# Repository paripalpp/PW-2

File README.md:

# PW-2
## parts
|     |     |
| --- | --- |
C7								|10n
C9, C10							|100u
C6, C8, C11						|1n
C1, C12                      	|10u
C2, C3, C5, C13, C16, C19-C25	|100n
C14, C15						|22p
C4, C17, C18					|1u
D1								|D
D2								|D_TVS
D3								|LED
D4-D7							|WS2812C
F1-F4							|Fuse
FL1								|BNX022
J1								|T_conn_male
J3								|USB_A_Stacked
J5								|2x07_P1.27mm_SMD
J6, J7							|S04B-XASK-1
J2, J8							|T_conn_female
J9-J13							|PinHeader_1x02_P2.54mm
J14-J20							|S02B-XASK-1
JP1								|SolderJumper_3_Bridged12
JP2-JP6							|SolderJumper_2_Open
L1								|8.2uH
Q1								|IPT007N06N
Q2, Q3							|TPH11006NL
R1								|100k
R4, R7, R8, R11, R12			|5k
R13								|100
R2, R3, R5, R6, R9, R10, R14-R16	|10k
R17								|120
R18								|10
R19								|330
RV1								|2.2k_Potentiometer
SW1								|SW_Push
SW2, SW3						|SW_SPDT
U1								|L7812
U2								|NCP1034
U3								|L78L12_SOT89
U4								|MCP1700-3302E_SOT23
U5								|STM32F303K8Tx
U6								|IM920s
U7								|MCP2551-I-SN
U8								|TLP152
Y1								|16MHz

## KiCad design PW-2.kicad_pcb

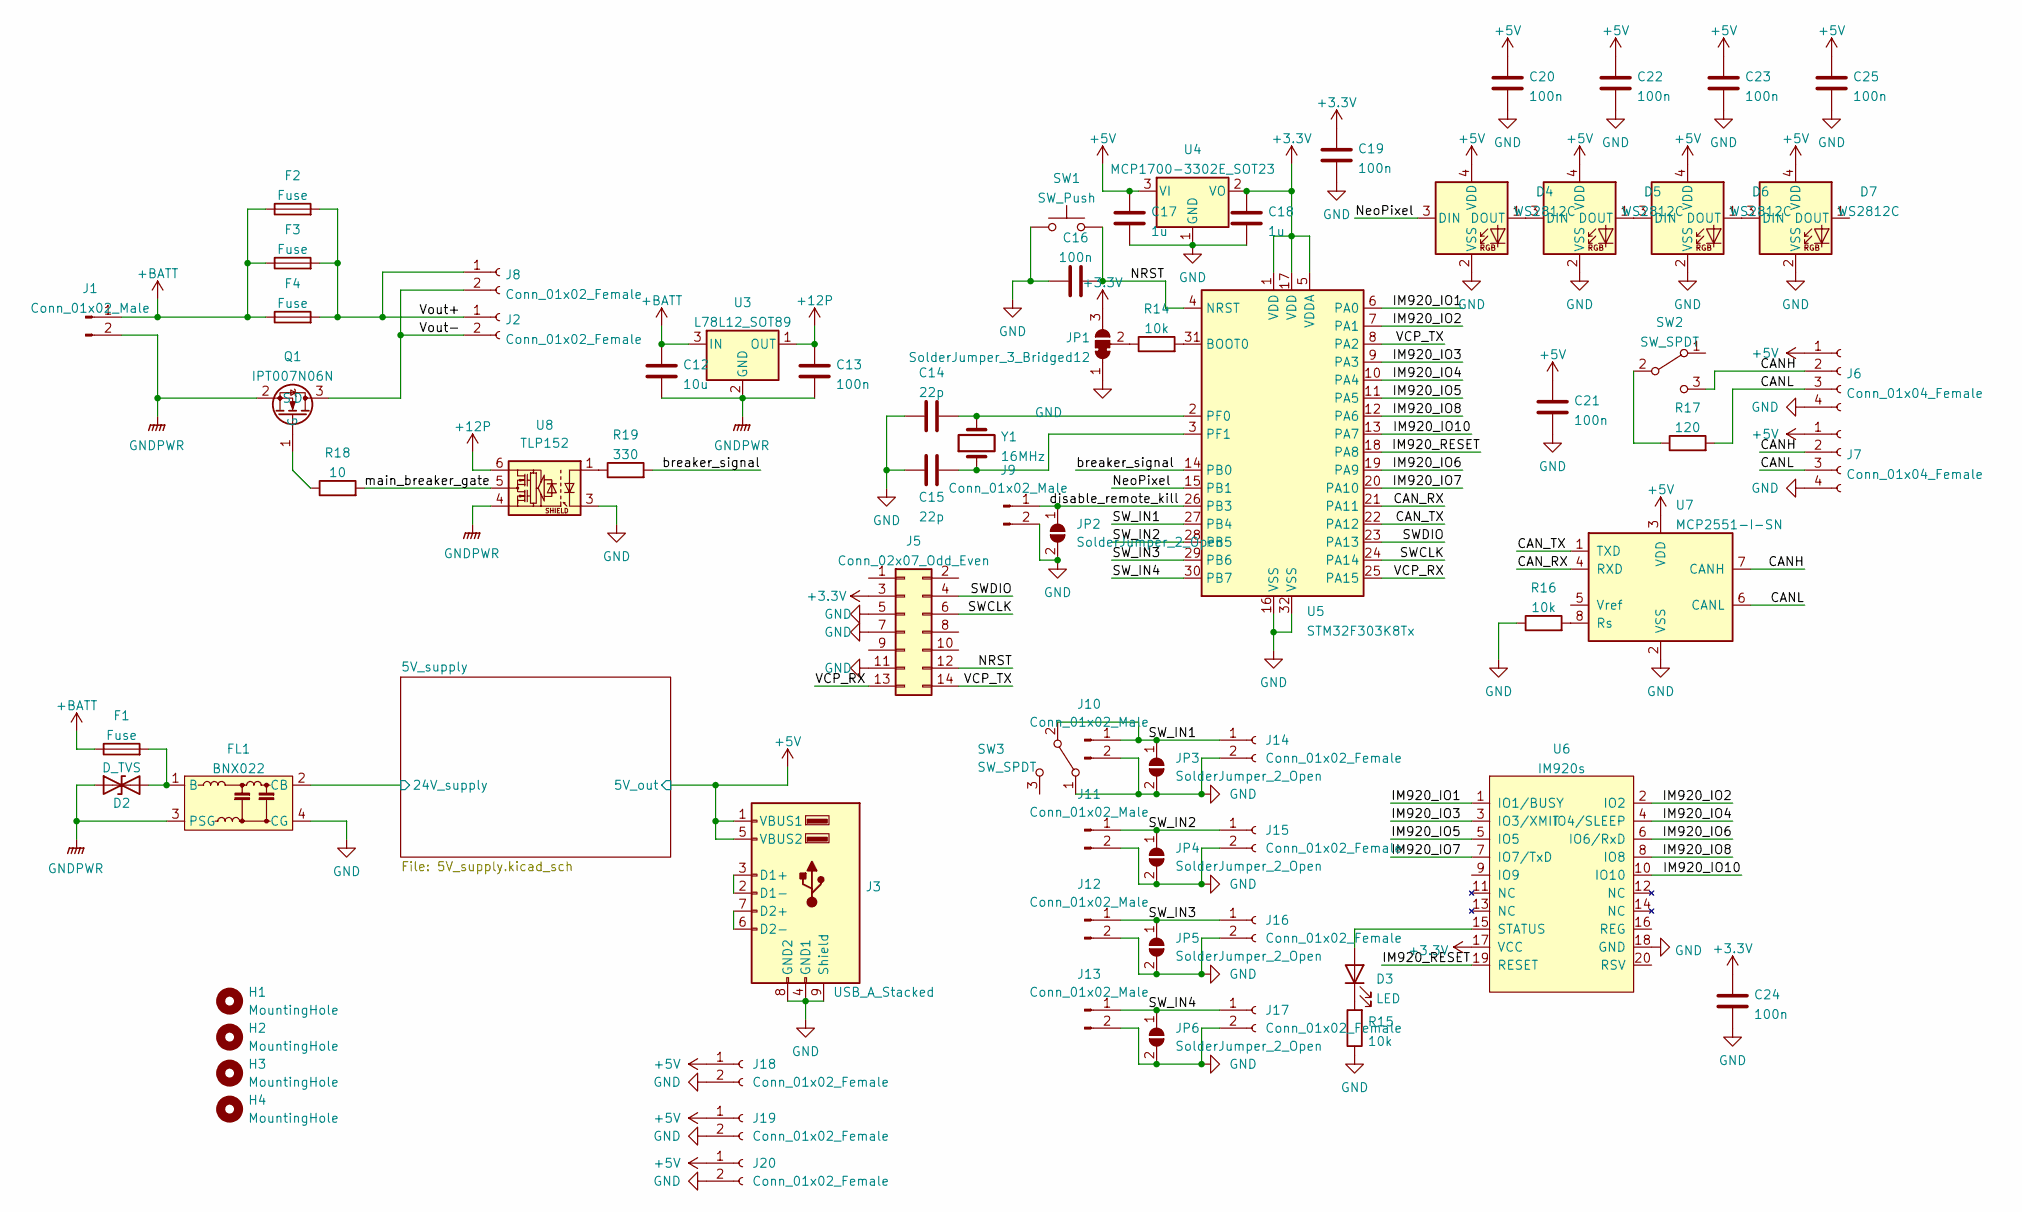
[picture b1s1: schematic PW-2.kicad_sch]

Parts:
C12: 10u; C_0805_2012Metric
C13, C16, C19, C20, C21, C22, C23, C24, C25: 100n; C_0603_1608Metric
C14, C15: 22p; C_0603_1608Metric
C17, C18: 1u; C_0603_1608Metric
D2: D_TVS; D_SMA
D3: LED; R_0603_1608Metric
D4, D5, D6, D7: WS2812C; LED_2020Metric_WS2812C_2.0x2.0mm_P1.0mm
F1, F2, F3, F4: Fuse; Fuseholder_Keystone_3568
FL1: BNX022; Filter_Murata_BNX025_ThermalVias
H1, H2, H3, H4: MountingHole; MountingHole_3.2mm_M3_Pad_Via
J1: Conn_01x02_Male; T_connecter_male_horizontal
J2, J8: Conn_01x02_Female; T_connecter_female_horizontal
J3: USB_A_Stacked; USB_A_Wuerth_61400826021_Horizontal_Stacked
J5: Conn_02x07_Odd_Even; PinHeader_2x07_P1.27mm_Vertical_SMD
J6, J7: Conn_01x04_Female; JST_XA_S04B-XASK-1_1x04_P2.50mm_Horizontal
J9, J10, J11, J12, J13: Conn_01x02_Male; PinHeader_1x02_P2.54mm_Vertical
J14, J15, J16, J17, J18, J19, J20: Conn_01x02_Female; JST_XA_S02B-XASK-1_1x02_P2.50mm_Horizontal
JP1: SolderJumper_3_Bridged12; SolderJumper-3_P1.3mm_Bridged12_RoundedPad1.0x1.5mm
JP2, JP3, JP4, JP5, JP6: SolderJumper_2_Open; SolderJumper-2_P1.3mm_Open_RoundedPad1.0x1.5mm
Q1: IPT007N06N; Infineon_PG-HSOF-8-1
R14, R15, R16: 10k; R_0603_1608Metric
R17: 120; R_0603_1608Metric
R18: 10; R_0603_1608Metric
R19: 330; R_0603_1608Metric
SW1: SW_Push; TVAF06-A020B-R
SW2, SW3: SW_SPDT; IS-1245T-G
U3: L78L12_SOT89; SOT-89-3
U4: MCP1700-3302E_SOT23; SOT-23
U5: STM32F303K8Tx; LQFP-32_7x7mm_P0.8mm
U6: IM920s
U7: MCP2551-I-SN; SOIC-8_3.9x4.9mm_P1.27mm
U8: TLP152; SO-6_5pin_4.4x3.6mm_P1.27mm
Y1: 16MHz; Crystal_SMD_HC49-SD

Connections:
+3V3: C18.2, C19.2, C24.2, J5.3, JP1.3 (B), U4.2 (VO), U5.1 (VDD), U5.5 (VDDA), U5.17 (VDD), U6.17 (VCC)
+5V: C17.2, C20.2, C21.2, C22.2, C23.2, C25.2, D4.4 (VDD), D5.4 (VDD), D6.4 (VDD), D7.4 (VDD), J3.1 (VBUS1), J3.5 (VBUS2), J6.1, J7.1, J18.1, J19.1, J20.1, U4.3 (VI), U7.3 (VDD); also elsewhere on the board
+12P: C13.2, U3.1 (OUT), U8.6
+BATT: C12.1, F1.1, F2.1, F3.1, F4.1, J1.1, U3.3 (IN)
/5V_supply/24V_supply: FL1.2 (CB); also elsewhere on the board
/CANH: J6.2, J7.2, SW2.3 (C), U7.7 (CANH)
/CANL: J6.3, J7.3, R17.2, U7.6 (CANL)
/CAN_RX: U5.21 (PA11), U7.4 (RXD)
/CAN_TX: U5.22 (PA12), U7.1 (TXD)
/IM920_IO1: U5.6 (PA0), U6.1 (IO1/BUSY)
/IM920_IO2: U5.7 (PA1), U6.2 (IO2)
/IM920_IO3: U5.9 (PA3), U6.3 (IO3/XMIT)
/IM920_IO4: U5.10 (PA4), U6.4 (IO4/SLEEP)
/IM920_IO5: U5.11 (PA5), U6.5 (IO5)
/IM920_IO6: U5.19 (PA9), U6.6 (IO6/RxD)
/IM920_IO7: U5.20 (PA10), U6.7 (IO7/TxD)
/IM920_IO8: U5.12 (PA6), U6.8 (IO8)
/IM920_IO10: U5.13 (PA7), U6.10 (IO10)
/IM920_RESET: U5.18 (PA8), U6.19 (RESET)
/NRST: C16.2, J5.12, SW1.2, U5.4 (NRST)
/NeoPixel: D4.3 (DIN), U5.15 (PB1)
/SWCLK: J5.6, U5.24 (PA14)
/SWDIO: J5.4, U5.23 (PA13)
/SW_IN1: J10.1, J14.1, JP3.1 (A), SW3.2 (B), U5.27 (PB4)
/SW_IN2: J11.1, J15.1, JP4.1 (A), U5.28 (PB5)
/SW_IN3: J12.1, J16.1, JP5.1 (A), U5.29 (PB6)
/SW_IN4: J13.1, J17.1, JP6.1 (A), U5.30 (PB7)
/VCP_RX: J5.13, U5.25 (PA15)
/VCP_TX: J5.14, U5.8 (PA2)
/Vout+: F2.2, F3.2, F4.2, J2.1, J8.1
/Vout-: J2.2, J8.2, Q1.3 (D)
/breaker_signal: R19.2, U5.14 (PB0)
/disable_remote_kill: J9.1, JP2.1 (A), U5.26 (PB3)
/main_breaker_gate: R18.2, U8.5
GND: C14.1, C15.1, C16.1, C17.1, C18.1, C19.1, C20.1, C21.1, C22.1, C23.1, C24.1, C25.1, D4.2 (VSS), D5.2 (VSS), D6.2 (VSS), D7.2 (VSS), FL1.4 (CG), J3.4 (GND1), J3.8 (GND2), J3.9 (Shield), J5.5, J5.7, J5.11, J6.4, J7.4, J9.2, J10.2, J11.2, J12.2, J13.2, J14.2, J15.2, J16.2, J17.2, J18.2, J19.2, J20.2, JP1.1 (A), JP2.2 (B), JP3.2 (B), JP4.2 (B), JP5.2 (B), JP6.2 (B), R15.1, R16.1, SW1.1, SW3.1 (A), U4.1 (GND), U5.16 (VSS), U5.32 (VSS), U6.18 (GND), U7.2 (VSS), U8.3; also elsewhere on the board
GNDPWR: C12.2, C13.1, D2.1 (A1), FL1.3 (PSG), J1.2, Q1.2 (S), U3.2 (GND), U8.4
unnamed: C14.2, U5.2 (PF0), Y1.2
unnamed: C15.2, U5.3 (PF1), Y1.1
unnamed: D2.2 (A2), F1.2, FL1.1 (B)
unnamed: D3.1 (K), R15.2
unnamed: D3.2 (A), U6.15 (STATUS)
unnamed: D4.1 (DOUT), D5.3 (DIN)
unnamed: D5.1 (DOUT), D6.3 (DIN)
unnamed: D6.1 (DOUT), D7.3 (DIN)
unnamed: J3.2 (D1-), J3.3 (D1+)
unnamed: J3.6 (D2-), J3.7 (D2+)
unnamed: JP1.2 (C), R14.1
unnamed: Q1.1 (G), R18.1
unnamed: R14.2, U5.31 (BOOT0)
unnamed: R16.2, U7.8 (Rs)
unnamed: R17.1, SW2.2 (B)
unnamed: R19.1, U8.1

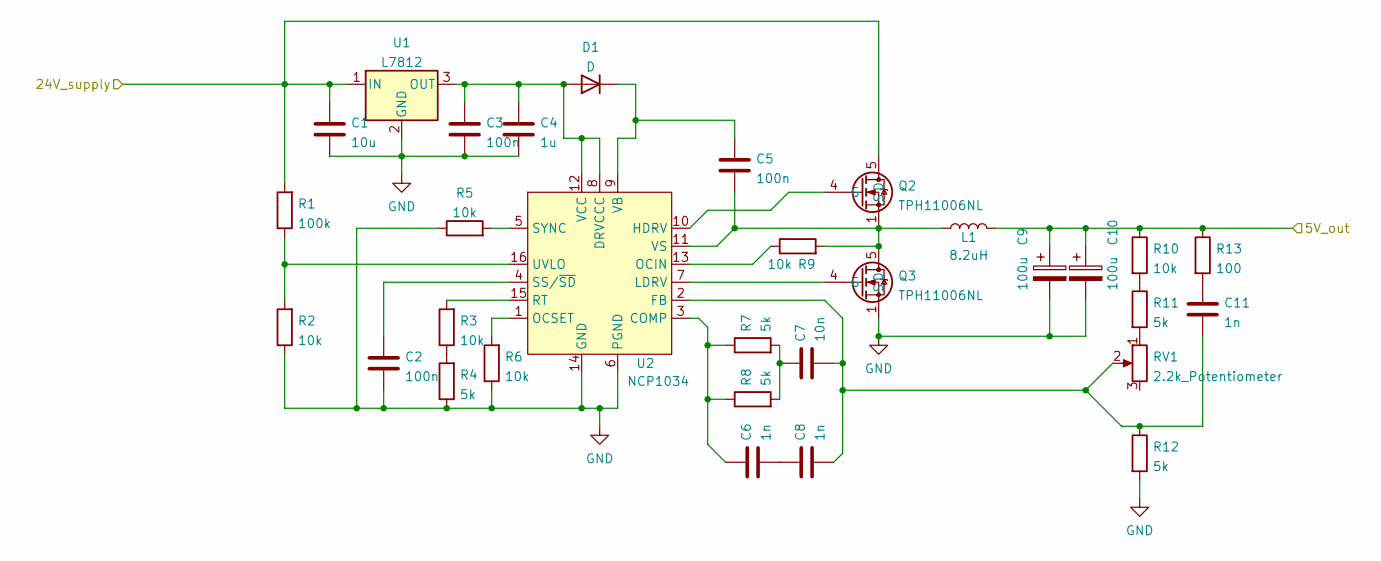
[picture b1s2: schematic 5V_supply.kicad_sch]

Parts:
C1: 10u; C_0805_2012Metric
C2, C3, C5: 100n; C_0603_1608Metric
C4: 1u; C_0603_1608Metric
C6, C8, C11: 1n; C_0603_1608Metric
C7: 10n; C_0603_1608Metric
C9, C10: 100u; CP_Elec_6.3x7.7
D1: D; D_SOD-123
L1: 8.2uH; L_Vishay_IHLP-6767
Q2, Q3: TPH11006NL; Toshiba_SOP_Advance
R1: 100k; R_0603_1608Metric
R2, R3, R5, R6, R9, R10: 10k; R_0603_1608Metric
R4, R7, R8, R11, R12: 5k; R_0603_1608Metric
R13: 100; R_0603_1608Metric
RV1: 2.2k_Potentiometer; Potentiometer_Murata_PVZ3A
U1: L7812; TO-252-2
U2: NCP1034; SOIC-16_3.9x9.9mm_P1.27mm

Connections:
+5V: C9.1, C10.1, L1.2, R10.1, R13.1; also elsewhere on the board
/5V_supply/24V_supply: C1.1, Q2.5 (D), Q2.6 (D), Q2.7 (D), Q2.8 (D), R1.2, U1.1 (IN); also elsewhere on the board
GND: C1.2, C2.2, C3.2, C4.2, C9.2, C10.2, Q3.1 (S), Q3.2 (S), Q3.3 (S), R2.1, R4.1, R5.1, R6.1, R12.2, U1.2 (GND), U2.6 (PGND), U2.14 (GND); also elsewhere on the board
unnamed: C2.1, U2.4 (SS/~SD)
unnamed: C3.1, C4.1, D1.2 (A), U1.3 (OUT), U2.8 (DRVCCC), U2.12 (VCC)
unnamed: C5.1, D1.1 (K), U2.9 (VB)
unnamed: C5.2, L1.1, Q2.1 (S), Q2.2 (S), Q2.3 (S), Q3.5 (D), Q3.6 (D), Q3.7 (D), Q3.8 (D), R9.2, U2.11 (VS)
unnamed: C6.1, R7.1, R8.1, U2.3 (COMP)
unnamed: C6.2, C8.1
unnamed: C7.2, R7.2, R8.2
unnamed: C11.1, R13.2
unnamed: C7.1, C8.2, C11.2, R12.1, RV1.2, U2.2 (FB)
unnamed: Q2.4 (G), U2.10 (HDRV)
unnamed: Q3.4 (G), U2.7 (LDRV)
unnamed: R1.1, R2.2, U2.16 (UVLO)
unnamed: R3.1, R4.2
unnamed: R3.2, U2.15 (RT)
unnamed: R5.2, U2.5 (SYNC)
unnamed: R6.2, U2.1 (OCSET)
unnamed: R9.1, U2.13 (OCIN)
unnamed: R10.2, R11.1
unnamed: R11.2, RV1.1

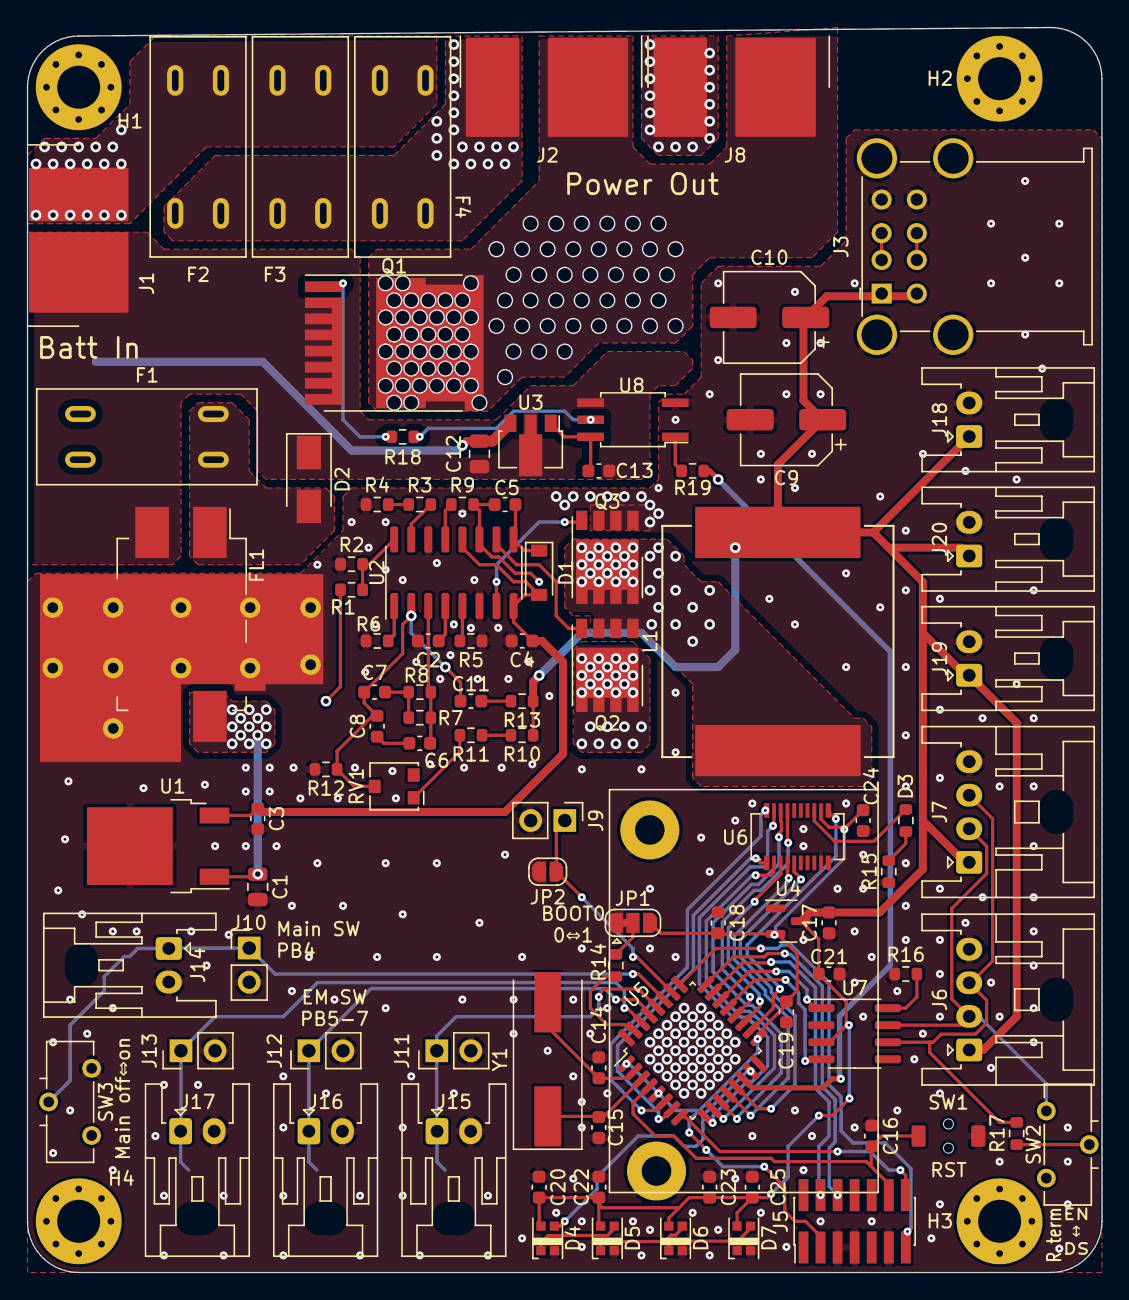
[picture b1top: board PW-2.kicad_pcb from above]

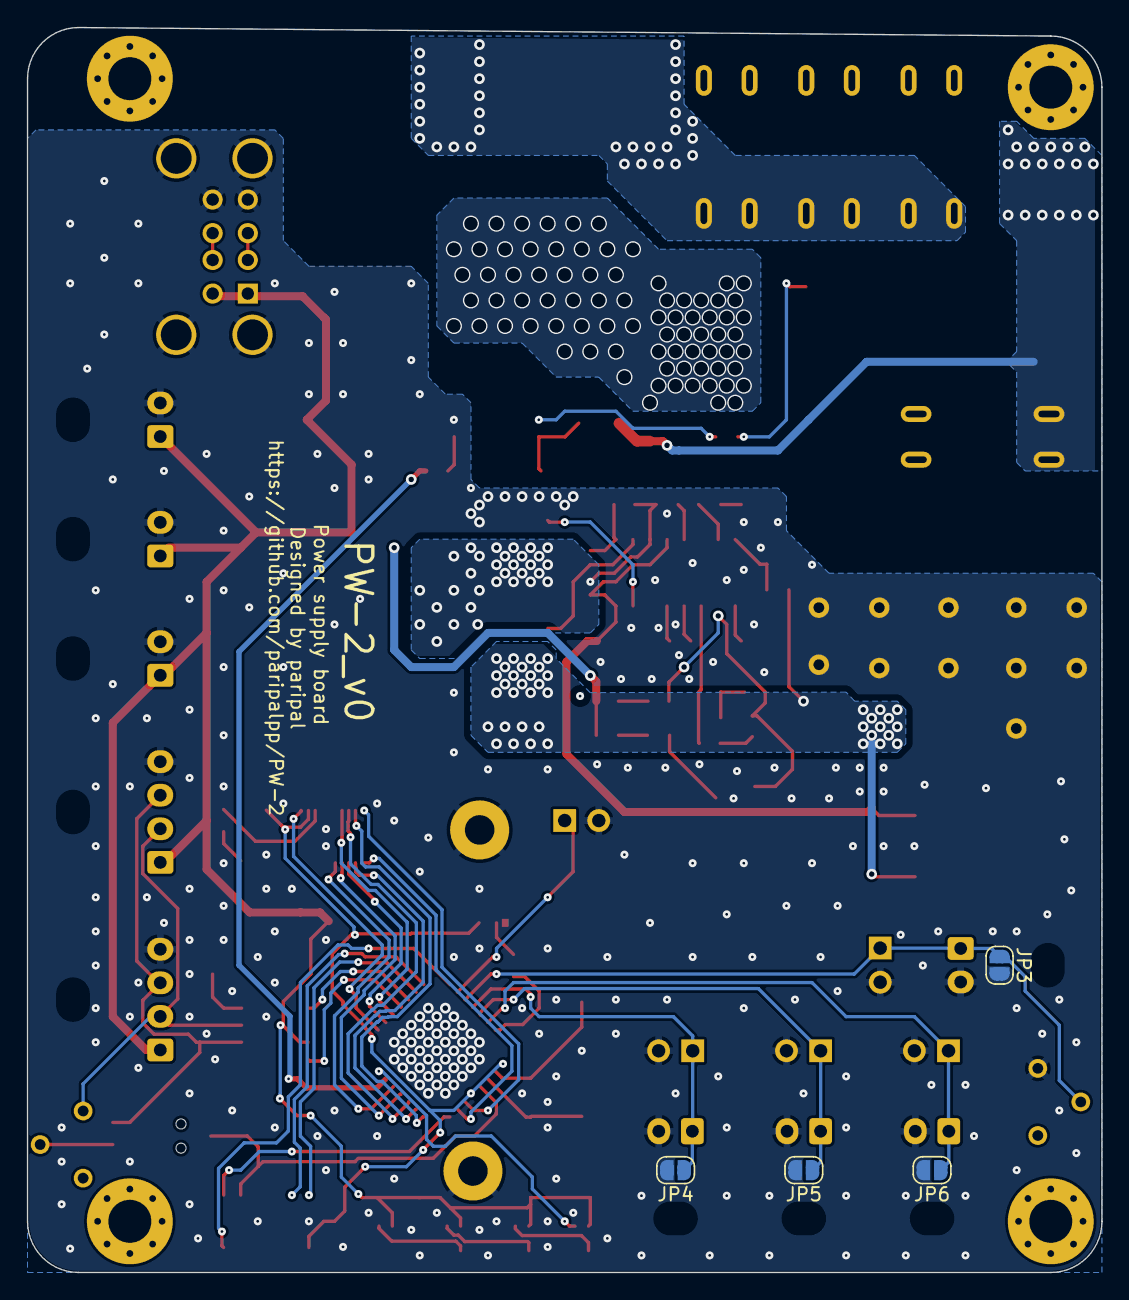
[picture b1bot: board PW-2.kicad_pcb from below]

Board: 2 copper layers, 80.0 x 92.7 mm, 102 parts (4 on the bottom side), 71 nets.

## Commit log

2022-05-03 some
2022-05-11 separate to some sheets
2022-05-13 little change
2022-06-22 DC-DC pram setted
2022-06-23 connectors
2022-07-01 many
2022-07-04 drawing around power done
2022-07-04 v0 done!
